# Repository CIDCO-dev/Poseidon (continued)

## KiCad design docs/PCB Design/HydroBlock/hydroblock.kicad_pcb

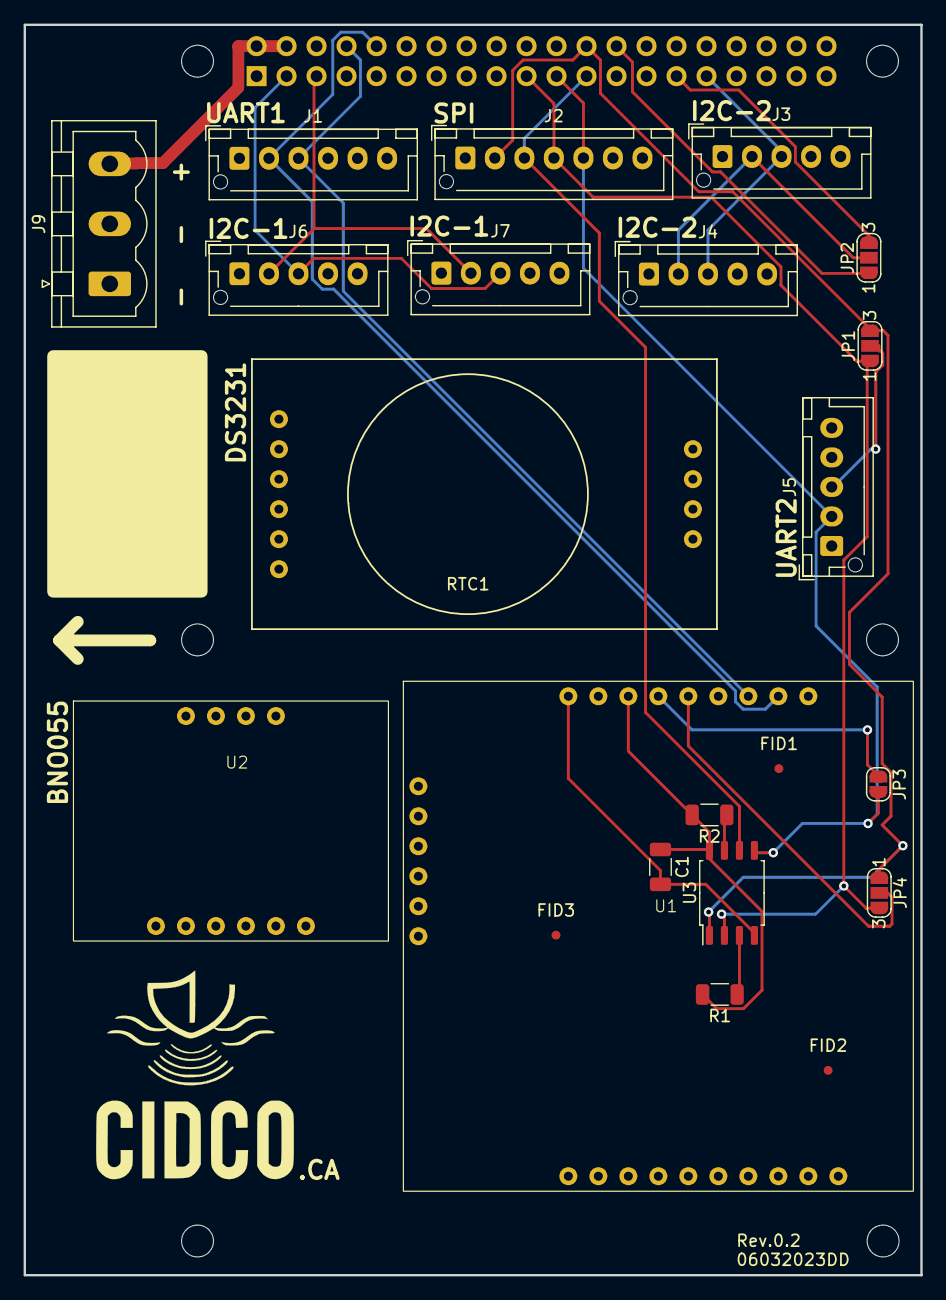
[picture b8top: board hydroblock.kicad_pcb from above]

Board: 4 copper layers, 75.9 x 105.9 mm, 30 parts (1 on the bottom side), 21 nets.

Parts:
C1: 100nF; C_1206_3216Metric
FID1, FID2, FID3: Fiducial; Fiducial_0.75mm_Mask2.25mm
J1: Conn_01x05; JST_XH_B6B-XH-AM_1x06_P2.50mm_Vertical
J2: Conn_01x07; JST_XH_B7B-XH-AM_1x07_P2.50mm_Vertical
J3, J4, J6, J7: Conn_01x05; JST_XH_B5B-XH-AM_1x05_P2.50mm_Vertical
J5: Conn_01x06; JST_XH_B5B-XH-AM_1x05_P2.50mm_Vertical
J8: Raspberry_Pi_2_3; PinSocket_2x20_P2.54mm_Vertical
J9: Conn_01x03; PhoenixContact_MSTBVA_2,5_3-G-5,08_1x03_P5.08mm_Vertical
JP1, JP2, JP4: SolderJumper_3_Open; SolderJumper-3_P1.3mm_Open_RoundedPad1.0x1.5mm_NumberLabels
JP3: SolderJumper_2_Open; SolderJumper-2_P1.3mm_Open_RoundedPad1.0x1.5mm
R1, R2: 10K; R_1206_3216Metric
REF1, REF2, REF3, REF4, REF5, REF6: MountingHole_2.7mm_M2.5_DIN965
RTC1: RTC_DS3231
U1: zed-f9p
U2: bno055
U3: W25Q32JVSS; SOIC-8_5.23x5.23mm_P1.27mm
logo1: LOGO; logo cidco

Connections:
+3.3V: C1.1, J1.5, J2.6, J3.4, J4.4, J5.4, J6.4, J7.4, J8.1 (3V3), J8.17 (3V3), R1.2, R2.2, RTC1.2 (VCC), U1.2 (3.3v), U1.13 (3.3v), U1.23 (3.3v), U2.1 (3.3v), U3.8 (VCC)
+5V: J1.6, J2.7, J3.5, J4.5, J5.5, J6.5, J7.5, J8.2 (5V), J8.4 (5V), J9.3
GND: C1.2, J1.1, J2.1, J3.1, J4.1, J5.1, J6.1, J7.1, J8.6 (GND), J8.9 (GND), J8.14 (GND), J8.20 (GND), J8.25 (GND), J8.30 (GND), J8.34 (GND), J8.39 (GND), J9.1, J9.2, RTC1.1 (GND), U1.1 (Gnd), U1.11 (Gnd), U1.25 (Gnd), U2.3 (gnd), U3.4 (GND)
unnamed: J3.2, J4.2, JP2.2 (C)
unnamed: J5.3, JP1.2 (C)
unnamed: JP3.1 (A), U1.14 (tx2)
unnamed: JP4.2 (C), U1.15 (rx2)
unnamed: R1.1, U3.3 (IO2)
unnamed: R2.1, U3.7 (IO3)
PPS: J1.4, J8.7 (GCLK0/GPIO4), U1.7 (pps)
SCK1: J6.2, J7.2, J8.5 (SCL/GPIO3), RTC1.4 (SCL), U2.5 (scl)
SCL4: J8.26 (~CE1/GPIO7), JP2.1 (A)
SCL6: J8.29 (GCLK1/GPIO5), JP2.3 (B)
SCLK: J2.3, J8.23 (SCLK0/GPIO11), U3.6 (CLK)
SDA1: J6.3, J7.3, J8.3 (SDA/GPIO2), RTC1.3 (SDA), U2.4 (sda)
SDA2: J3.3, J4.3, J8.31 (GCLK2/GPIO6)
U1RX: J1.2, J8.10 (GPIO15/RXD), U1.18 (tx1)
U1TX: J1.3, J8.8 (GPIO14/TXD), U1.17 (rx1)
U2RX/MISO: J2.5, J5.2, J8.21 (MISO0/GPIO9), JP3.2 (B), U3.5 (DI(IO0))
U2TX/CE0: J2.2, J8.24 (~CE0/GPIO8), JP1.3 (B), JP4.1 (A), U3.1 (~CS)
U2TX/MOSI: J2.4, J8.19 (MOSI0/GPIO10), JP1.1 (A), JP4.3 (B), U3.2 (DO(IO1))

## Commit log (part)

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2024-02-22 serial baud rate threaded
2024-02-22 serial baud rate
2024-02-22 serial baud rate setting
2024-02-28 water infiltration node architecture
2024-02-28 lidar calib printer
2024-02-28 fix timestamp in sonar imagenex852 py
2024-02-28 work around the python installer script
2024-02-28 create log output dir if not there
2024-02-28 fix configuration change function
2024-02-28 Issue #350
2024-02-28 fix gnss path
2024-02-28 serial number diagnostic
2024-02-28 gnss_zed-f9p_config node was not functionnal (removed form repo) in tools new python script to aply the right configuration in command line in the ZED-F9P python script to validate the configuration
2024-02-28 add missing code comment c++ code
2024-02-28 fix sonar command value
2024-02-28 fix port not getting set at launch
2024-03-14 sonar_imagenex852_c start
2024-03-25 making progress
2024-03-26 https support
2024-03-27 logging binary sonar
2024-03-27 debug binary sonar data
2024-04-02 apiKey can be changed via ui
2024-04-05 dataPoints arg imagegenex
2024-05-07 Adding helper script to replace the ssid of the Hotspot
2024-05-07 update directory in docs and add more information about the power recuirement and use in the hydroblock
2024-05-07 update docs and remove unused stuff
2024-05-09 DC-DC converter datasheet
2024-05-20 few correction in the vital node and add a collor in the status web page
2024-06-28 ssl version debug
2024-07-22 Geofence
2024-07-23 Semicolon
2024-08-05 add doccumentation in the script to set the serial number
2024-08-20 new 852 node
2024-08-29 HIH8130 chip in vitals
2024-09-03 revert change
2024-09-09 led controller
2024-09-10 logger call led controller service
2024-09-11 BinaryStreamGnssDiagnostic
2024-09-13 i2c controller + service
2024-09-16 logger led control
2024-09-17 led error triggers
2024-09-19 UI battery
2024-09-23 compile optim
2024-09-25 nofix signal + logger encapsulation
2024-09-25 fix: recording status signal do not override nofix signal
2024-10-01 initial tests ok
2024-10-02 service.waitForExistence()
2024-10-04 vitals + speed, logger text
2024-10-10 graceful shutdown
2024-10-29 #issue 389 - refactor wifi node
2024-10-31 i2c retrocompatibility
2024-11-01 Hide information in the system status web page
2024-11-01 fix geofence
2024-11-04 ROS is adding 2 param to each argv
2024-11-14 comment some ros messageto reduce log size
2024-11-18 Add fixes made by Patrick and add information hiden in the web page if the i1c sensor are not present
2024-11-21 fix ros error message
2024-11-22 fixe web interface for missing sensors
2024-11-22 fix in websocket and javascript for webinterface for #407
2024-11-22 work map.html for #408
2024-11-22 more work on javascript for #408
2024-11-22 more work on #408
2024-11-22 fix web page
2024-11-27 add button for Auto pan to current position
2024-11-28 add js script for wicket and terraformer to be able to be loaded locally
2024-12-02 Update User manual screen capture.
2025-02-10 fix error
2025-02-10 add new dataset in websocket
2025-02-10 fix led state
2025-02-11 move the code in the right function
2025-02-11 update battery formula on status webpage
2025-02-11 remove the loffing of the error
2025-02-11 fix error on sonar no value
2025-02-11 code cleaning
2025-02-11 HydroBlock Installation Manual and User Manual HydroBlock PCB Rev 1 Led Module PCB Rev 0
2025-02-11 Cleaning directory
2025-02-11 HydroB PCB Rev 0.3 Module bypass rev 1.0 Module power rev 1.0
2025-02-11 HydroB rev 0.5
2025-02-11 Firmware for the power module of the hydroball
2025-02-11 Led driver Obsolete, led is drived directly by gpio
2025-02-12 fix nodes to control eht led with the GPIO
2025-02-12 PCB Production files
2025-02-27 update the power module programmer interface to be able to power the power module from a usb port if programmed with an atmel ice programmer
2025-02-27 PCB HB-HAT : fix mosfet pinout
2025-03-04 incrase debug output
2025-03-04 update warning and critical message for the web interface
2025-03-05 no led at boot when we alredy have gps fix
2025-03-05 fix the condition for the humidity on the web interface
2025-03-10 fix condition for shut down and translate and update the comment
2025-03-19 fix battery voltage treshold
2025-03-19 fix voltage bar on the system status web page
2025-03-19 fix the battery voltage from 13.5 to 11.9v in the web interface
2025-04-10 fix i2c4 configuration
2025-04-22 add gnss telemetry in the node of the zed-f9p
2025-04-23 gnss status on the dashboard working
2025-04-24 first file transfered manualy by the web interface
2025-04-24 fix dependencu for curl
2025-05-14 fix 500ms offset betwen systemclock and gnss clock
2025-08-26 diagnostics
2025-11-07 cpp_import
2025-12-01 fix ICMP ping from google to ubuntu, to reduce the amount of host route.
2025-12-01 fix sonar node name
2025-12-01 install git in the ci
2025-12-01 add ros-noetic-roslint ros-noetic-nodelet ros-noetic-dynamic-reconfigure ros-noetic-sensor-msgs in the ci installation
2025-12-01 fix binairy logger variable location and test
2025-12-01 add node list and test script
2025-12-01 add ros-noetic-sbg-driver in the CI installation
2025-12-01 add func list in manifest.md
2025-12-01 blacklist imu_bno055 node and rpivitals fix launch file for the logger test
2025-12-01 fix dependency for file websocket
2025-12-01 first test for the workflow
2025-12-01 add libwebsocketpp-dev in the ci installation
2025-12-01 add libopencv-dev libexiv2-dev libboost-signals-dev to ci installation
2025-12-01 add definition in data websocket test
2025-12-01 fix source error in the ci
2025-12-01 fix dependencies and force catkinmake in -j1
2025-12-01 remove libboost-signals-dev from ci installation
2025-12-01 fix requirement for the logger test
2025-12-01 add a dep for test purpose
2025-12-01 test correction for logger service
2025-12-01 add nmea0183 test
2025-12-01 add filwwebsocket in blacklist
2025-12-01 add test in the nmea0183 node
2025-12-01 Fix build dep and ci
2025-12-01 fix dependencies(
2025-12-01 JS tests: added explicit `jest-environment-jsdom` devDependency to satisfy Jest config.
2025-12-01 JS housekeeping: generated package-lock for reproducible installs and removed committed coverage output; keep coverage artifacts untracked.
2025-12-01 - Fixed logger text test build by defining `currentRssBytes` helper in `test_logger_text_node.cpp`.
2025-12-01 Logger: transfer loop now counts zip files once, reports status, sends, and removes on success; RapidJSON string creation simplified.
2025-12-01 - Updated agent guidelines: C++ formatting/lint (`clang-format`, `clang-tidy`) now tracked in the Review & PR checklist. - Updated agent guidelines: Python formatting (`black`) added to the Review & 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
2025-12-01 CI: Coverage summary now runs from a separate script `.github/workflows/scripts/coverage_summary.py`.
2025-12-01 CI: GitHub Actions now posts C++/Python/JS coverage summary to the workflow summary.
2025-12-01 fix dependencies...
2025-12-01 add dependencies and fix logger test
2025-12-01 add tests on logger node
2025-12-01 CI: Coverage summary heredoc anchored with indentation (python block).
2025-12-01 Build fix: added `binary_stream_msg` dependency to diagnostics package (resolves missing `binary_stream_msg/Stream.h` include).
2025-12-01 Docs: added `doc/install.md` detailing prerequisites and install steps for RPi4 Ubuntu 20.04.
2025-12-01 JS: VM-based Jest tests now instrument scripts before execution so coverage is reported correctly (no longer 0%).
2025-12-01 CI: coverage summary now also falls back to JS lcov when coverage-summary.json is missing (ensures JS coverage is reported).
2025-12-01 CI: coverage summary surfaces test totals/errors/failures and lists failing suites (links to junit-test-results artifact).
2025-12-01 Remove ROS1→ROS2 port attempt
2025-12-01 raspberrypi_vitals: ensure targets depend on generated messages (catkin_EXPORTED_TARGETS) and declare i2c_controller_service in CATKIN_DEPENDS to fix missing `raspberrypi_vitals_msg/sysinfo.h` during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
2025-12-01 cleaning of diagnostics
2025-12-01 - diagnostics: install the websocket integration test script via catkin so rostest can locate/execute it. - ROS tests: add pytest skip guards for ROS-dependent Python tests to avoid failures when ROS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
2025-12-01 Launch: replace missing `diagnostics_node` with `diagnostics_websocket.py` in Hydrobox/Hydroball/Simulator launch files to fix diagnostics startup errors.
2025-12-01 diagnostics: fix `getRunningNodes` handler to unpack publisher/subscriber/service lists correctly (no more "too many values to unpack").
2025-12-02 - Web UI: System Status now shows wlan0 state + SSID using sysfs/proc+iwgetid (no nmcli dependency in telemetry path). - hydroball_data_websocket: publish Wi‑Fi status/SSID in telemetry payload (`tel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
2025-12-02 - diagnostics: added unit tests for the diagnostics websocket node (commands, node listing, lifecycle helpers) to cover its behaviors without ROS master dependencies.
2025-12-02 - install: fixed `ethernet_move_hotspot_rpi4.sh` variable handling (no more escaped `$`/awk errors) and robust interface-name replacement in Hotspot.nmconnection.
2025-12-02 launch: All Hydrobox profiles now start `wifi_file_transfer_config_node` so Wi‑Fi provisioning is consistent across RPi/Rock and simulator setups.
2025-12-02 - hydroball_data_websocket: use nmcli to populate Wi‑Fi SSID/state, drop iwgetid dependency, and clear SSID when disconnected.
2025-12-02 - Web UI (status): Wi‑Fi row now matches other bars (full-width gradient green/red) with SSID in the header and connection state inline, instead of a separate dot/text block.
2025-12-02 - Web UI (status): Wi‑Fi row matches other bars (full-width gradient green/red) with SSID + state inline in the header; bar color now follows `wifi.state` up/down.
2025-12-09 - diagnostics: added end-to-end nosetest that launches `launchROSService.sh`, waits for the 9099 diagnostics websocket, sends `updateDiagnostic`, and validates the returned payload; optional DBT feed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
2025-12-18 - diagnostics: start the WebSocket server from inside the asyncio loop to be compatible with newer `websockets` versions (fixes port 9099 not opening on some systems).
2025-12-18 - launch/e2e: pass `loggerPath` and `configPath` from `POSEIDON_LOGGER_PATH` / `POSEIDON_CONFIG_PATH` via `launchROSService.sh` (avoids invalid nested `$(optenv ...)` substitutions in roslaunch args).
2025-12-18 - diagnostics/e2e: make IMU/sonar communication thresholds configurable via env vars (`POSEIDON_DIAG_IMU_*`, `POSEIDON_DIAG_SONAR_*`) to reduce false negatives on slower benches. - e2e: allow tuning 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
2025-12-18 - e2e: keep a DBT NMEA writer running for the whole E2E so `/depth` can be validated when `DIAGNOSTICS_FAKE_SERIAL_PORT` is available. - e2e: optional exclusive mode (`POSEIDON_E2E_EXCLUSIVE=1`) stop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
2026-01-12 - e2e: require root launch by default (`POSEIDON_E2E_LAUNCH_AS_ROOT=1`) and reuse the already-started service during the E2E run to avoid duplicate roslaunch. - diagnostics/e2e: honor `POSEIDON_E2E_L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
2026-02-28 Bump minimatch from 3.1.2 to 3.1.5 in /www/webroot/js
    Bumps [minimatch](https://github.com/isaacs/minimatch) from 3.1.2 to 3.1.5.
    - [Changelog](https://github.com/isaacs/minimatch/blob/main/changelog.md)
    - [Commits](https://github.com/isaacs/minimatch/compare/v3.1.2...v3.1.5)
    ---
    updated-dependencies:
    - dependency-name: minimatch
